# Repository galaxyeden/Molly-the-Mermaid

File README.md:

# Molly the Mermaid

Molly the Mermaid is my 2022 badge project, following on from 2020's [Candy the Catacorn](https://galaxyallie.space/Candy-the-Catacorn/).

- Mermaid tail PCB intended to be used with a hand-made mermaid body for customization.
- Raspberry Pi Pico used as a module to provide much functionality and enable easy assembly for beginners
- Intended completion April 2022
- Bright shiny things
- Gaming controls!
- [v1.69bis](https://hackaday.com/2019/03/20/introducing-the-shitty-add-on-v1-69bis-standard/) compliant-ish

## Bill of Materials

| Component                               | Manufacturer                 | Qty |
|-----------------------------------------|------------------------------|-----|
| This board                              | Whoever you choose           | 1   |
| Raspberry Pi Pico                       | Raspberry Pi                 | 1   |
| S2B-PH-SM4-TB(LF)(SN)                   | JST                          | 1   |
| 0.1uF 0805 Capacitor                    | Generic                      | 5   |
| WS2812b                                 | WorldSemi                    | 5   |
| LED 0805                                | Generic                      | 10  |
| DSS14UTR                                | SMC Diode Solutions          | 1   |
| 470 Ohm 0805 Resistor                   | Generic                      | 11  |
| TL3342 Switch (or equivalent)           | E-Switch (or generic)        | 6   |
| 2x3 2.54mm pin socket connector         | Generic                      | 1   |

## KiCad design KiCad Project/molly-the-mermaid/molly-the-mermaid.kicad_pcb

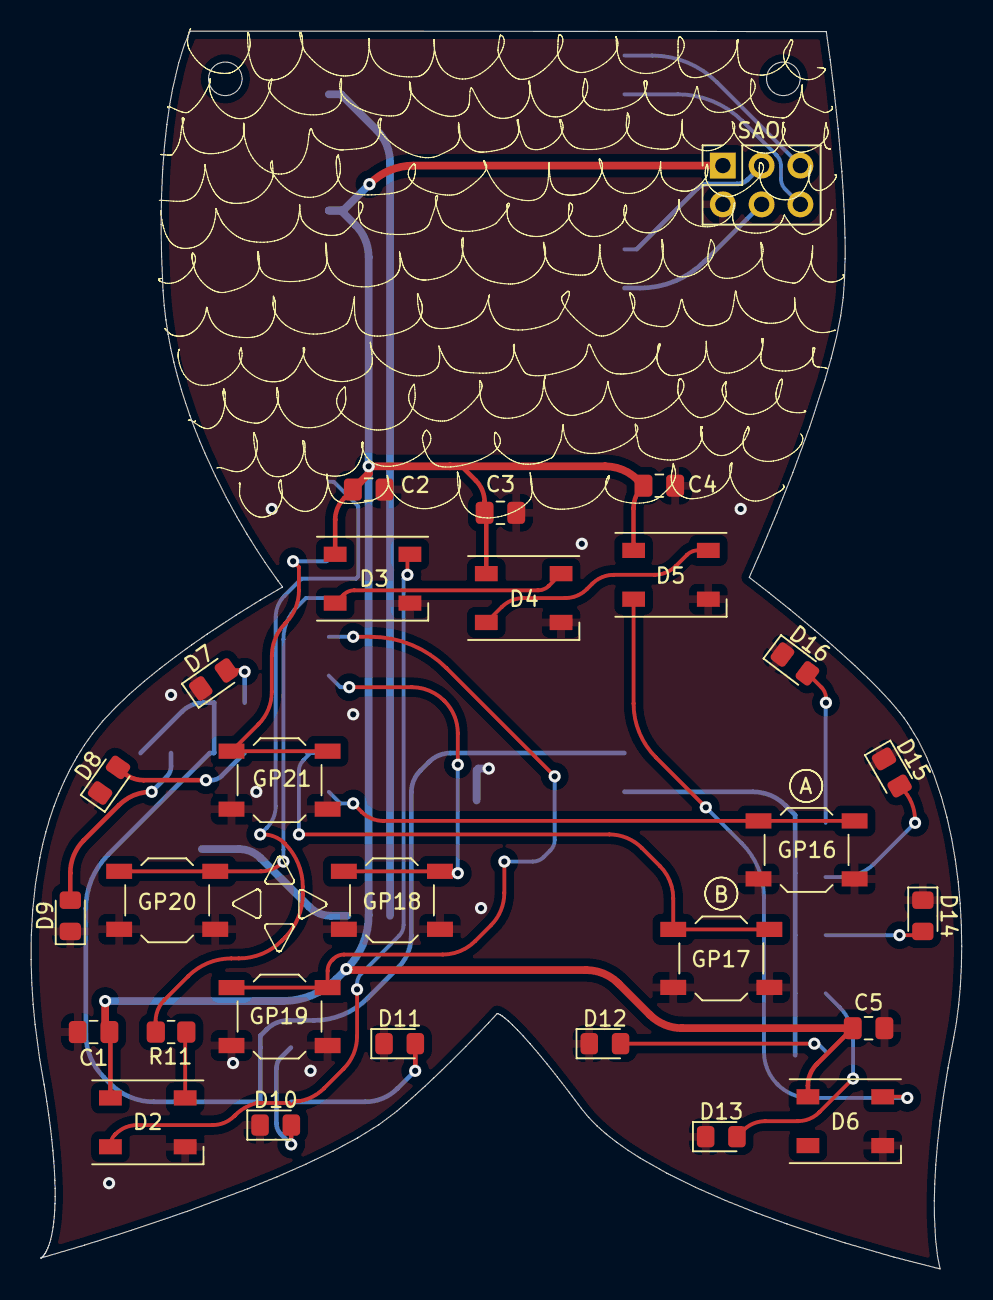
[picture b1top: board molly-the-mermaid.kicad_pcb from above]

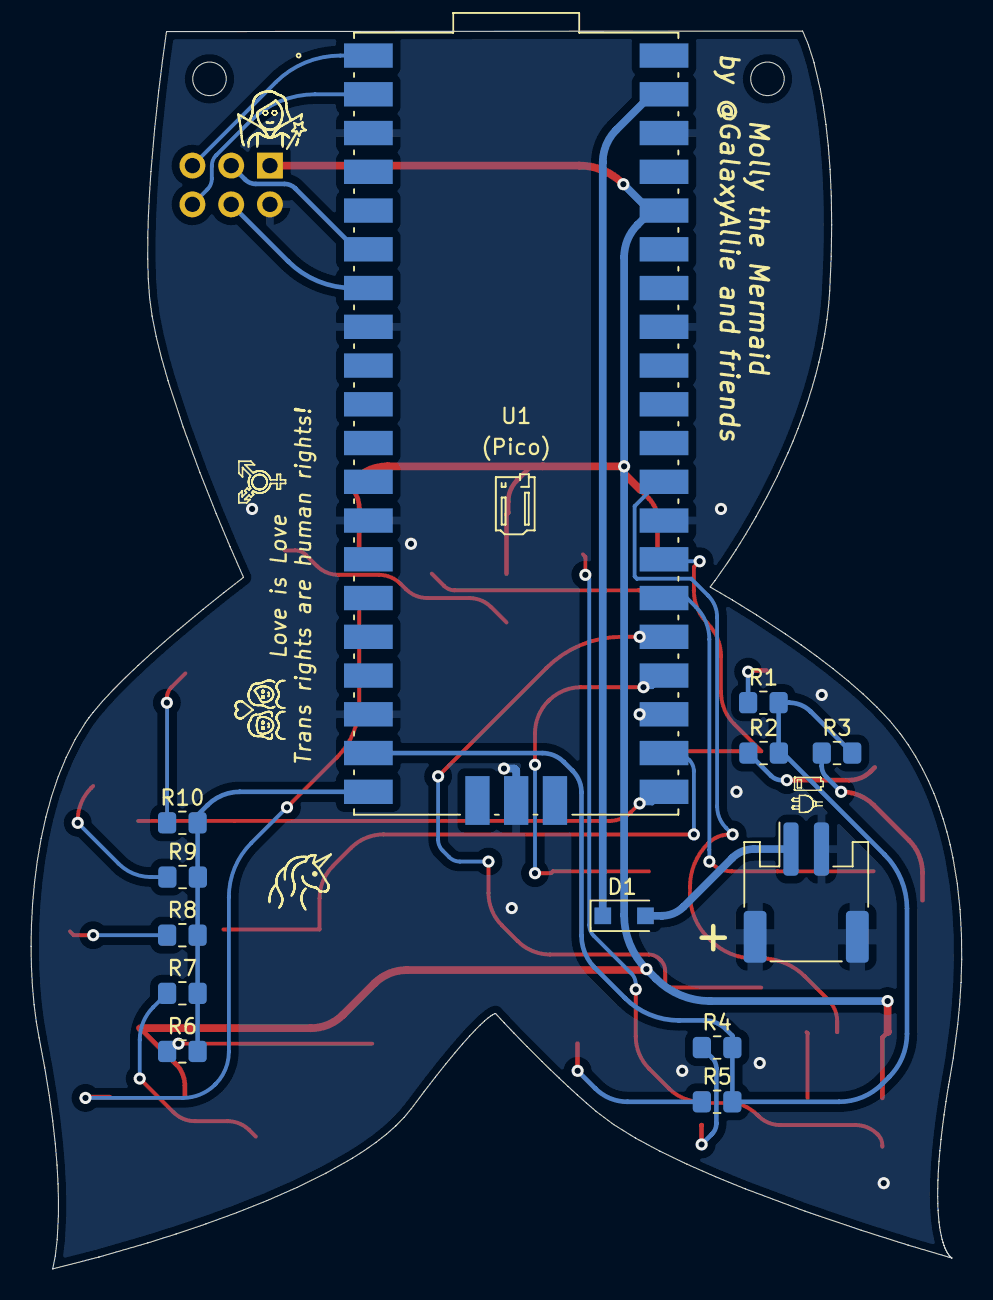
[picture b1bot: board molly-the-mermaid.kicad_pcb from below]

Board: 2 copper layers, 61.0 x 81.1 mm, 43 parts (13 on the bottom side), 32 nets.

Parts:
A: A; SW_SPST_TL3342
B: B; SW_SPST_TL3342
Battery: Battery; JST_PH_S2B-PH-SM4-TB_1x02-1MP_P2.00mm_Horizontal
C1, C2, C3, C4, C5: C; C_0805_2012Metric_Pad1.18x1.45mm_HandSolder
D1: D_Schottky; D_SOD-123F
D2, D3, D4, D5, D6: WS2812B; LED_WS2812B_PLCC4_5.0x5.0mm_P3.2mm
D7, D8, D9, D10, D11, D12, D13, D14, D15, D16: LED; LED_0805_2012Metric_Pad1.15x1.40mm_HandSolder
Down: Down; SW_SPST_TL3342
H1, H2: MountingHole; MountingHole_2.2mm_M2
Left: Left; SW_SPST_TL3342
R1, R2, R3, R4, R5, R6, R7, R8, R9, R10, R11: R; R_0805_2012Metric_Pad1.20x1.40mm_HandSolder
Right: Right; SW_SPST_TL3342
SAO: SAO; PinSocket_2x03_P2.54mm_Vertical
U1: (Pico); SC0915-No test pads
Up: Up; SW_SPST_TL3342

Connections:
+3V3: C1.1, C2.1, C3.1, C4.1, C5.1, D2.1 (VDD), D3.1 (VDD), D4.1 (VDD), D5.1 (VDD), D6.1 (VDD), SAO.1, U1.36 (3V3OUT)
+BATT: Battery.1 (+), D1.2 (A)
/LED_DATA_1: R11.1, U1.29 (GP22)
/SAO1: SAO.5, U1.1 (UART0_TX/I2C0_SDA/SPI0_RX/GP0)
/SAO2: SAO.6, U1.2 (UART0_RX/I2C0_SCL/GPI0_CSn/GP1)
/SCL: SAO.4, U1.7 (UART1_RX/I2C0_SCL/SPI0_CSn/GP5)
/SDA: SAO.3, U1.6 (UART1_TX/I2C0_SDA/SPI0_RX/GP4)
GND: A.2, B.2, Battery.2 (-), Battery.MP, C1.2, C2.2, C3.2, C4.2, C5.2, D2.3 (VSS), D3.3 (VSS), D4.3 (VSS), D5.3 (VSS), D6.3 (VSS), D7.1 (K), D8.1 (K), D9.1 (K), D10.1 (K), D11.1 (K), D12.1 (K), D13.1 (K), D14.1 (K), D15.1 (K), D16.1 (K), Down.2, Left.2, Right.2, SAO.2, U1.3 (GND), U1.8 (GND), U1.13 (GND), U1.18 (GND), U1.23 (GND), U1.28 (GND), U1.33 (AGND/GND), U1.38 (GND), U1.D2 (GND), Up.2
unnamed: D1.1 (K), U1.39 (VSYS)
unnamed: D2.2 (DOUT), D3.4 (DIN)
unnamed: D2.4 (DIN), R11.2
unnamed: D3.2 (DOUT), D4.4 (DIN)
unnamed: D4.2 (DOUT), D5.4 (DIN)
unnamed: D5.2 (DOUT), D6.4 (DIN)
unnamed: D7.2 (A), R1.1
unnamed: D8.2 (A), R2.1
unnamed: D9.2 (A), R3.1
unnamed: D10.2 (A), R4.1
unnamed: D11.2 (A), R5.1
unnamed: D12.2 (A), R6.1
unnamed: D13.2 (A), R7.1
unnamed: D14.2 (A), R8.1
unnamed: D15.2 (A), R9.1
unnamed: D16.2 (A), R10.1
unnamed: R1.2, R2.2, R3.2, R4.2, R5.2, U1.19 (I2C1_SDA/SPI1_SCK/GP14)
unnamed: R6.2, R7.2, R8.2, R9.2, R10.2, U1.20 (I2C1_SCL/SPI1_TX/GP15)
unnamed: Left.1, U1.26 (I2C0_SDA/GP20)
unnamed: U1.27 (I2C0_SCL/GP21), Up.1
unnamed: Right.1, U1.24 (I2C1_SDA/SPI0_SCK/GP18)
unnamed: Down.1, U1.25 (I2C1_SCL/SPI0_TX/GP19)
unnamed: B.1, U1.22 (UART0_RX/I2C0_SCL/SPI0_CSn/GP17)
unnamed: A.1, U1.21 (UART0_TX/I2C0_SDA/SPI0_RX/GP16)

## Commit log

2022-01-19 Create KiCad Project
2022-01-19 Customized footprint
2022-01-19 First draft
2022-01-19 1.0 schematic
2022-01-19 fixed 3V3
2022-01-20 board draft
2022-01-20 connected grounds
2022-01-20 another missing ground
2022-01-20 cleared some DRC errors
2022-01-20 add mounting holes
2022-01-20 Added component values to schematic
2022-01-20 Board draft 2
2022-01-20 moved SAO connector up
2022-01-21 Final draft board
2022-01-21 First production run version
2022-01-21 removed unused part
2022-01-21 added pico itself to BOM
2022-01-21 consistent wording
2022-03-09 Added CircuitPython code
2022-03-09 Add B button test that doesn't need external neopixels

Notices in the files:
parts and their libraries:
Copyright 2021 Accelerated Designs. All rights reserved.
